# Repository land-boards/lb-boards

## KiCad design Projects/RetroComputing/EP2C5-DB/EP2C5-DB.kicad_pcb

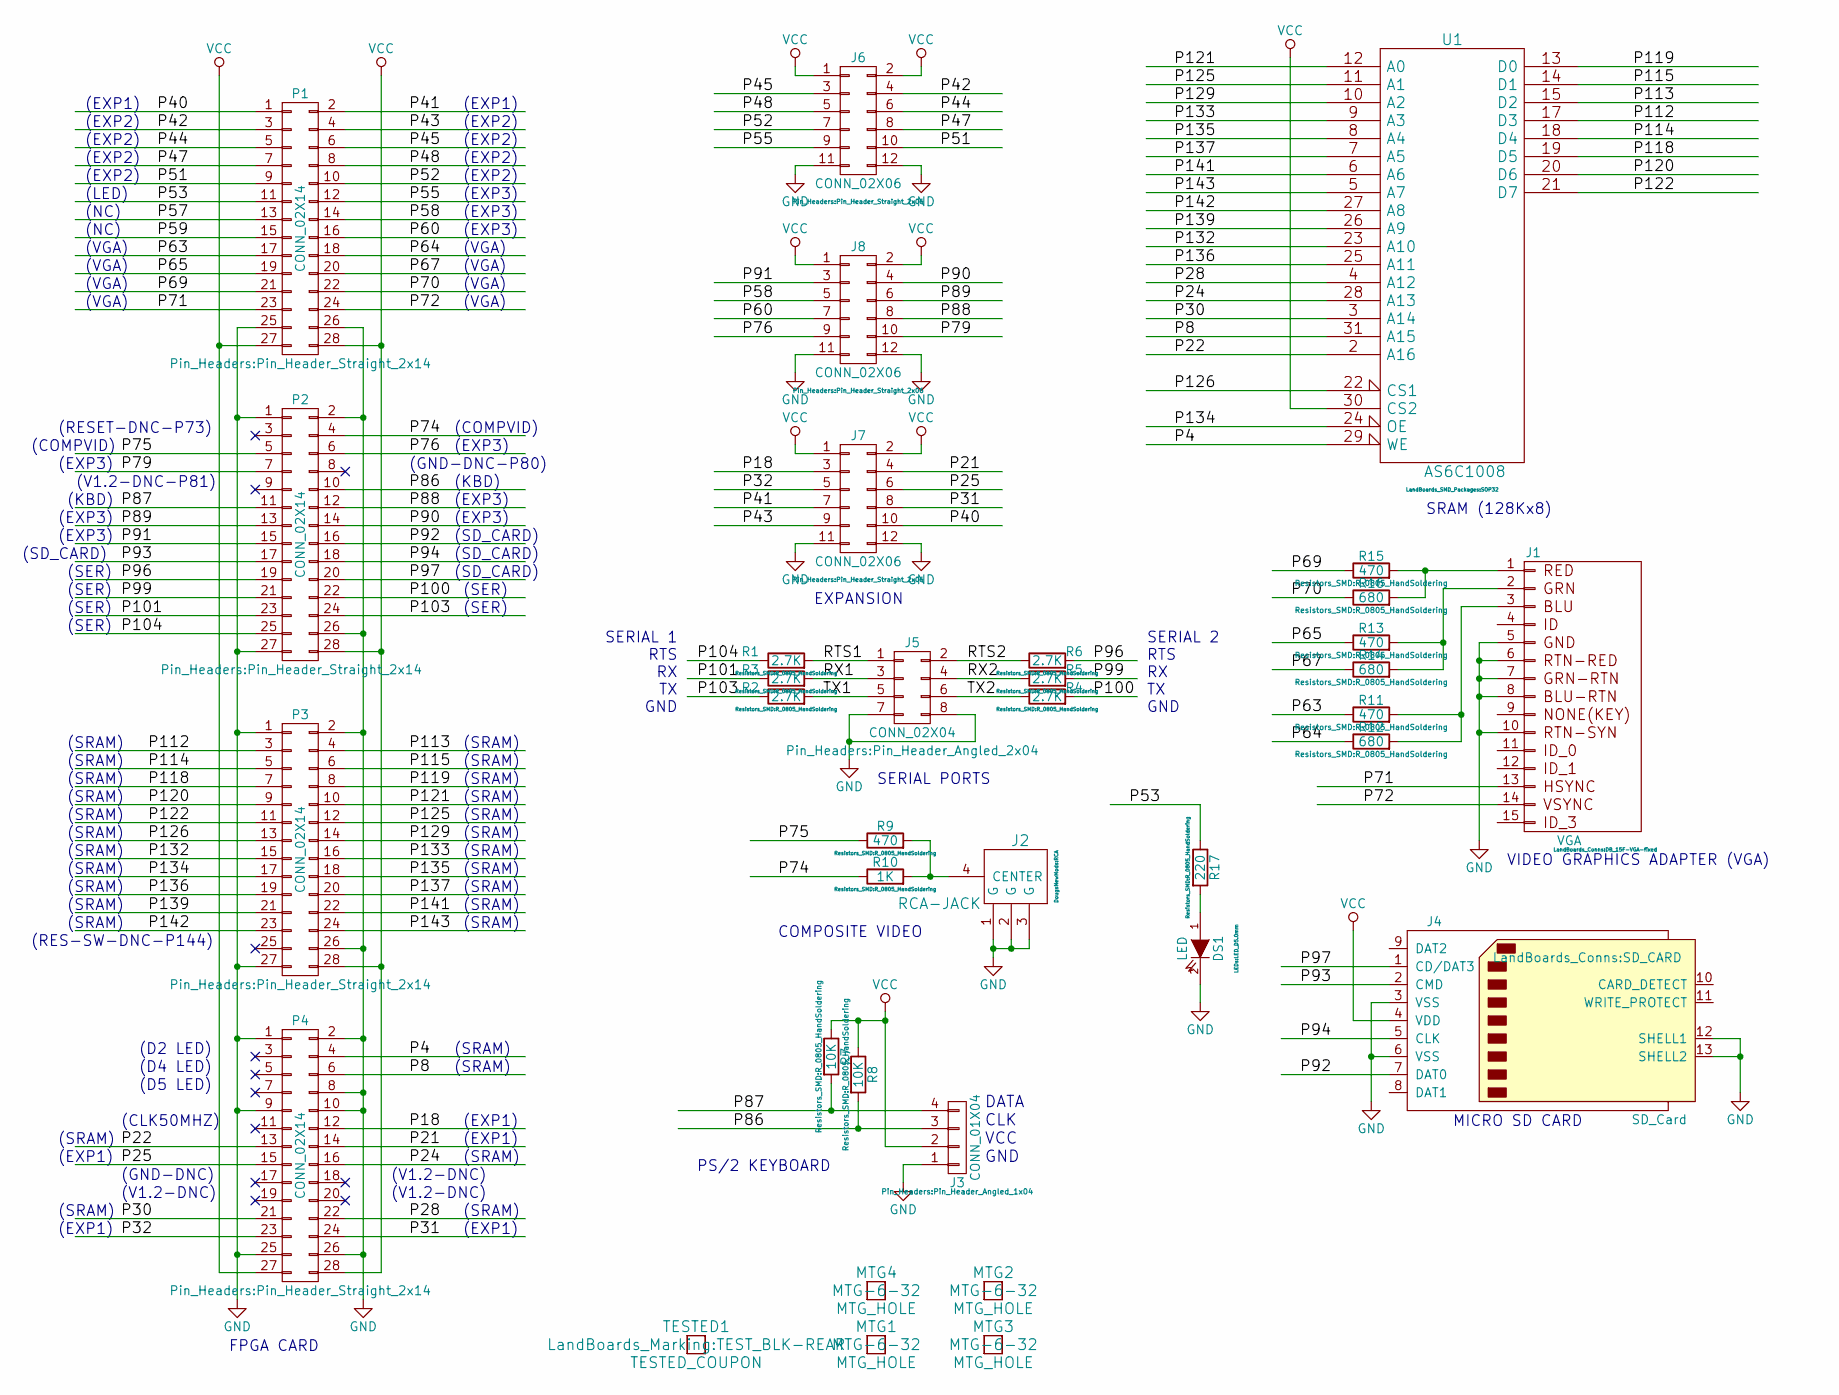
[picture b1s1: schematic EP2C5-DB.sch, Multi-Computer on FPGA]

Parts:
DS1: LED; LED_D5.0mm
J1: VGA; DB_15F-VGA-fixed
J2: RCA-JACK; RCA
J3: CONN_01X04; Pin_Header_Angled_1x04
J4: SD_Card; SD_CARD
J5: CONN_02X04; Pin_Header_Angled_2x04
J6, J7, J8: CONN_02X06; Pin_Header_Straight_2x06
MTG1, MTG2, MTG3, MTG4: MTG_HOLE; MTG-6-32
P1, P2, P3, P4: CONN_02X14; Pin_Header_Straight_2x14
R1, R2, R3, R4, R5, R6: 2.7K; R_0805_HandSoldering
R7, R8: 10K; R_0805_HandSoldering
R9, R11, R13, R15: 470; R_0805_HandSoldering
R10: 1K; R_0805_HandSoldering
R12, R14, R16: 680; R_0805_HandSoldering
R17: 220; R_0805_HandSoldering
TESTED1: TESTED_COUPON; TEST_BLK-REAR
U1: AS6C1008; SOP32

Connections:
/P4: P4.4, U1.29 (WE)
/P8: P4.6, U1.31 (A15)
/P18: J7.3, P4.12
/P21: J7.4, P4.14
/P22: P4.13, U1.2 (A16)
/P24: P4.16, U1.28 (A13)
/P25: J7.6, P4.15
/P28: P4.22, U1.4 (A12)
/P30: P4.21, U1.3 (A14)
/P31: J7.8, P4.24
/P32: J7.5, P4.23
/P40: J7.10, P1.1
/P41: J7.7, P1.2
/P42: J6.4, P1.3
/P43: J7.9, P1.4
/P44: J6.6, P1.5
/P45: J6.3, P1.6
/P47: J6.8, P1.7
/P48: J6.5, P1.8
/P51: J6.10, P1.9
/P52: J6.7, P1.10
/P53: P1.11, R17.1
/P55: J6.9, P1.12
/P58: J8.5, P1.14
/P60: J8.7, P1.16
/P63: P1.17, R11.1
/P64: P1.18, R12.1
/P65: P1.19, R13.1
/P67: P1.20, R14.1
/P69: P1.21, R15.1
/P70: P1.22, R16.1
/P71: J1.13, P1.23
/P72: J1.14, P1.24
/P74: P2.4, R10.1
/P75: P2.5, R9.1
/P76: J8.9, P2.6
/P79: J8.10, P2.7
/P86: J3.3, P2.10, R8.2
/P87: J3.4, P2.11, R7.2
/P88: J8.8, P2.12
/P89: J8.6, P2.13
/P90: J8.4, P2.14
/P91: J8.3, P2.15
/P92: J4.7 (DAT0), P2.16
/P93: J4.2 (CMD), P2.17
/P94: J4.5 (CLK), P2.18
/P96: P2.19, R6.2
/P97: J4.1 (CD/DAT3), P2.20
/P99: P2.21, R5.2
/P100: P2.22, R4.2
/P101: P2.23, R3.1
/P103: P2.24, R2.1
/P104: P2.25, R1.1
/P112: P3.3, U1.17 (D3)
/P113: P3.4, U1.15 (D2)
/P114: P3.5, U1.18 (D4)
/P115: P3.6, U1.14 (D1)
/P118: P3.7, U1.19 (D5)
/P119: P3.8, U1.13 (D0)
/P120: P3.9, U1.20 (D6)
/P121: P3.10, U1.12 (A0)
/P122: P3.11, U1.21 (D7)
/P125: P3.12, U1.11 (A1)
/P126: P3.13, U1.22 (CS1)
/P129: P3.14, U1.10 (A2)
/P132: P3.15, U1.23 (A10)
/P133: P3.16, U1.9 (A3)
/P134: P3.17, U1.24 (OE)
/P135: P3.18, U1.8 (A4)
/P136: P3.19, U1.25 (A11)
/P137: P3.20, U1.7 (A5)
/P139: P3.21, U1.26 (A9)
/P141: P3.22, U1.6 (A6)
/P142: P3.23, U1.27 (A8)
/P143: P3.24, U1.5 (A7)
/RTS1: J5.1, R1.2
/RTS2: J5.2, R6.1
/RX1: J5.3, R3.2
/RX2: J5.4, R5.1
/TX1: J5.5, R2.2
/TX2: J5.6, R4.1
GND: DS1.2 (K), J1.5, J1.6, J1.7, J1.8, J1.10, J2.1 (G), J2.2 (G), J2.3 (G), J3.1, J4.3 (VSS), J4.6 (VSS), J4.12 (SHELL1), J4.13 (SHELL2), J5.7, J5.8, J6.11, J6.12, J7.11, J7.12, J8.11, J8.12, P1.25, P1.26, P2.1, P2.2, P2.26, P2.27, P3.1, P3.2, P3.26, P3.27, P4.1, P4.2, P4.8, P4.9, P4.10, P4.25, P4.26, U1.16 (GND)
unnamed: DS1.1 (A), R17.2
unnamed: J1.1, R15.2, R16.2
unnamed: J1.2, R13.2, R14.2
unnamed: J1.3, R11.2, R12.2
unnamed: J2.4 (CENTER), R9.2, R10.2
VCC: J3.2, J4.4 (VDD), J6.1, J6.2, J7.1, J7.2, J8.1, J8.2, P1.27, P1.28, P2.28, P3.28, P4.27, P4.28, R7.1, R8.1, U1.30 (CS2), U1.32 (VCC)

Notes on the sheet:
SERIAL 1 RTS RX TX GND
SERIAL 2 RTS RX TX GND
DATA CLK VCC GND
PS/2 KEYBOARD
SRAM (128Kx8)
VIDEO GRAPHICS ADAPTER (VGA)
MICRO SD CARD
SERIAL PORTS
COMPOSITE VIDEO
FPGA CARD
EXPANSION
(CLK50MHZ)
(GND-DNC)
(GND-DNC-P80)
(V1.2-DNC-P81)
(D2 LED)
(D4 LED)
(D5 LED)
(RES-SW-DNC-P144)
(RESET-DNC-P73)
(V1.2-DNC)
(SRAM)
(EXP1)
(COMPVID)
(SD_CARD)
(KBD)
(SER)
(EXP2)
(EXP3)
(VGA)
(LED)
(NC)

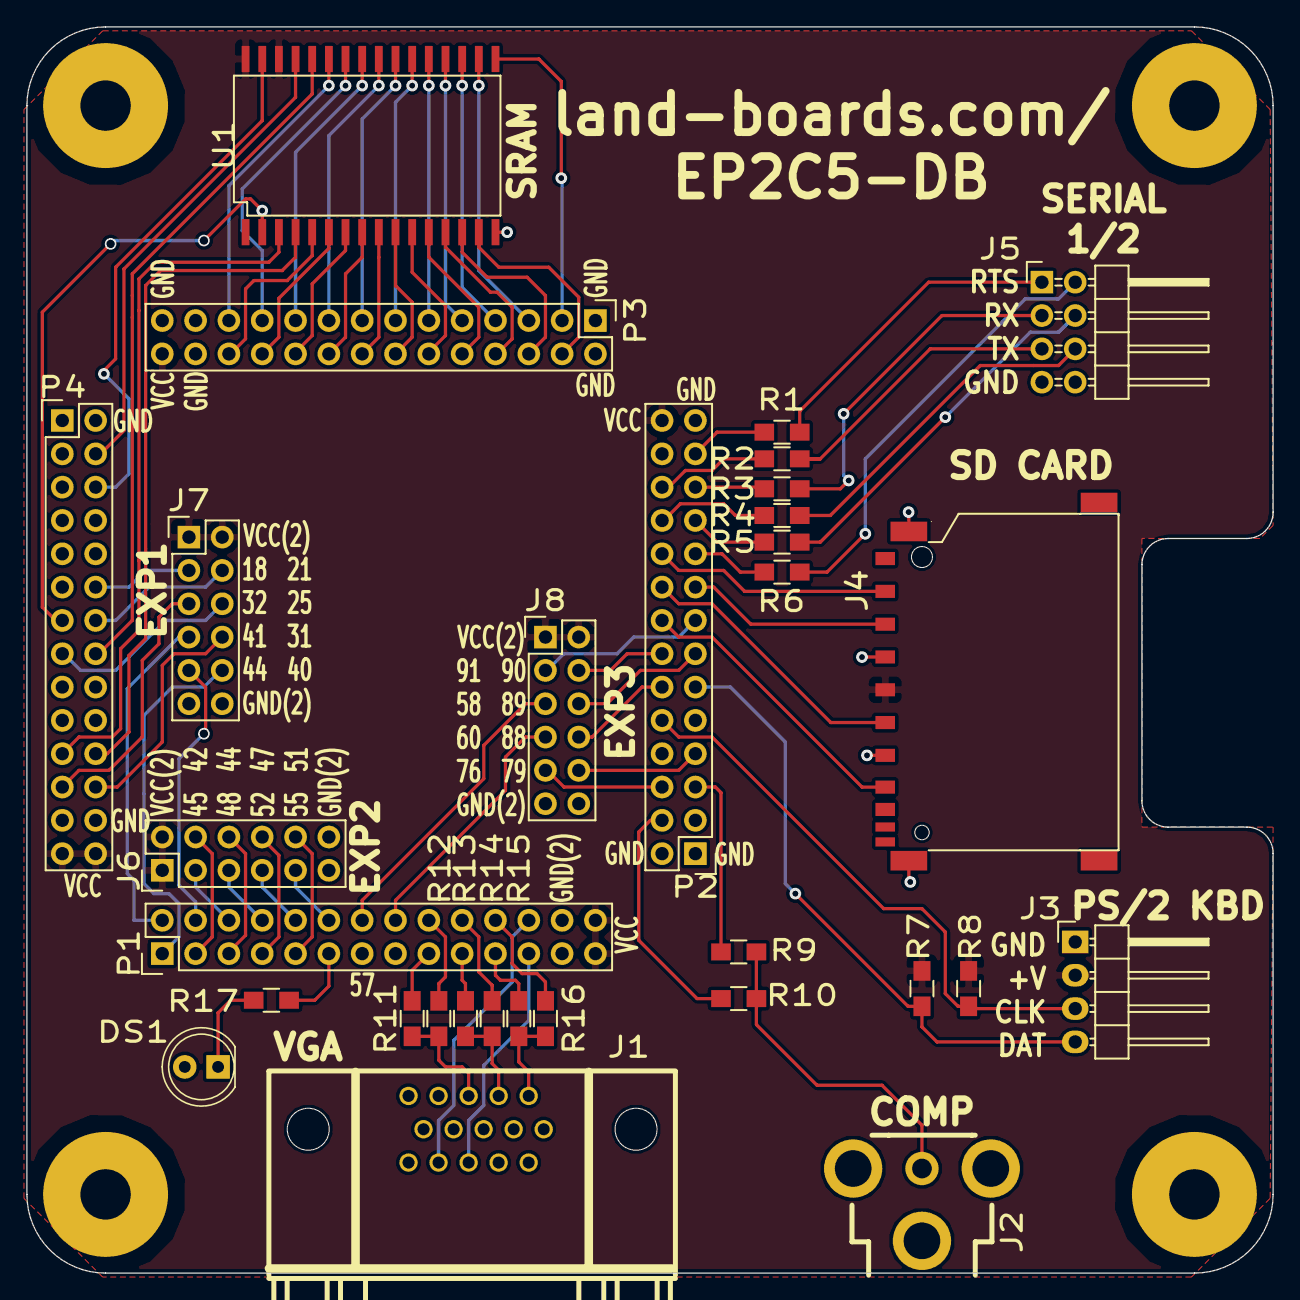
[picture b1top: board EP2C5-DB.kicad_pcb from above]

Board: 2 copper layers, 95.0 x 95.0 mm, 36 parts (0 on the bottom side), 88 nets.

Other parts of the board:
TESTED: TESTED_COUPON; TEST_BLK-REAR

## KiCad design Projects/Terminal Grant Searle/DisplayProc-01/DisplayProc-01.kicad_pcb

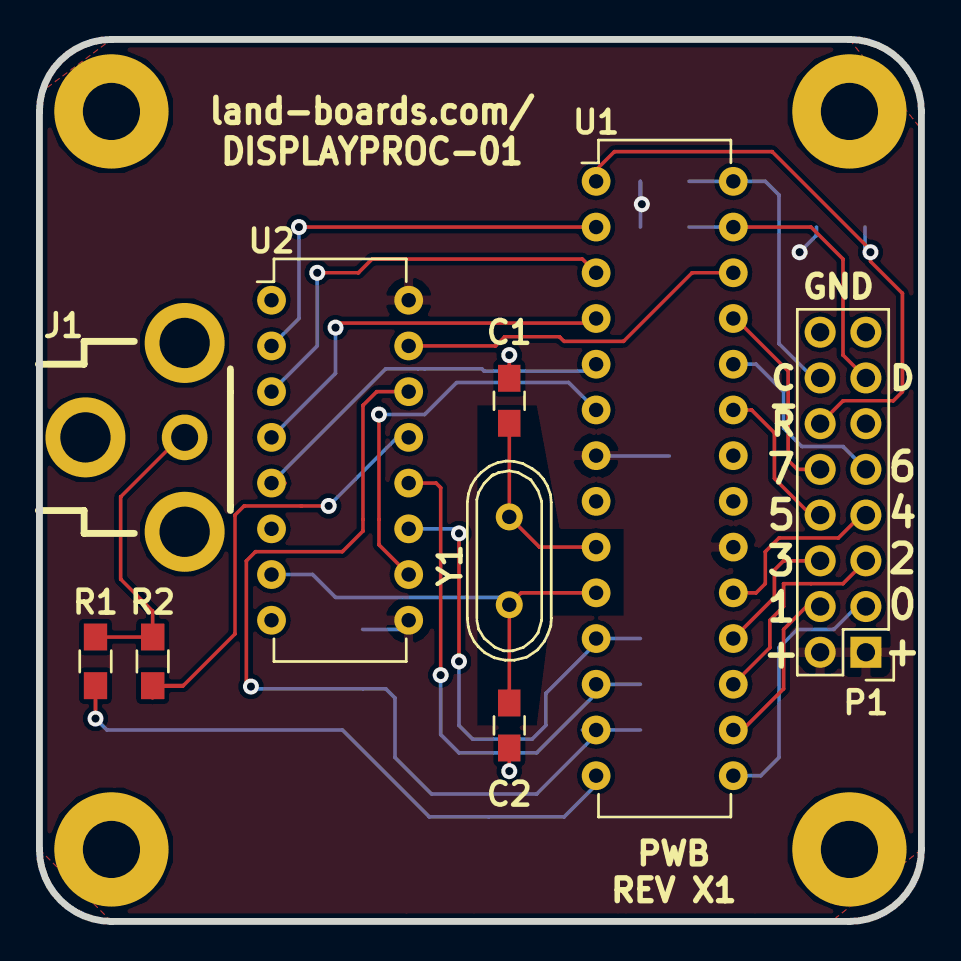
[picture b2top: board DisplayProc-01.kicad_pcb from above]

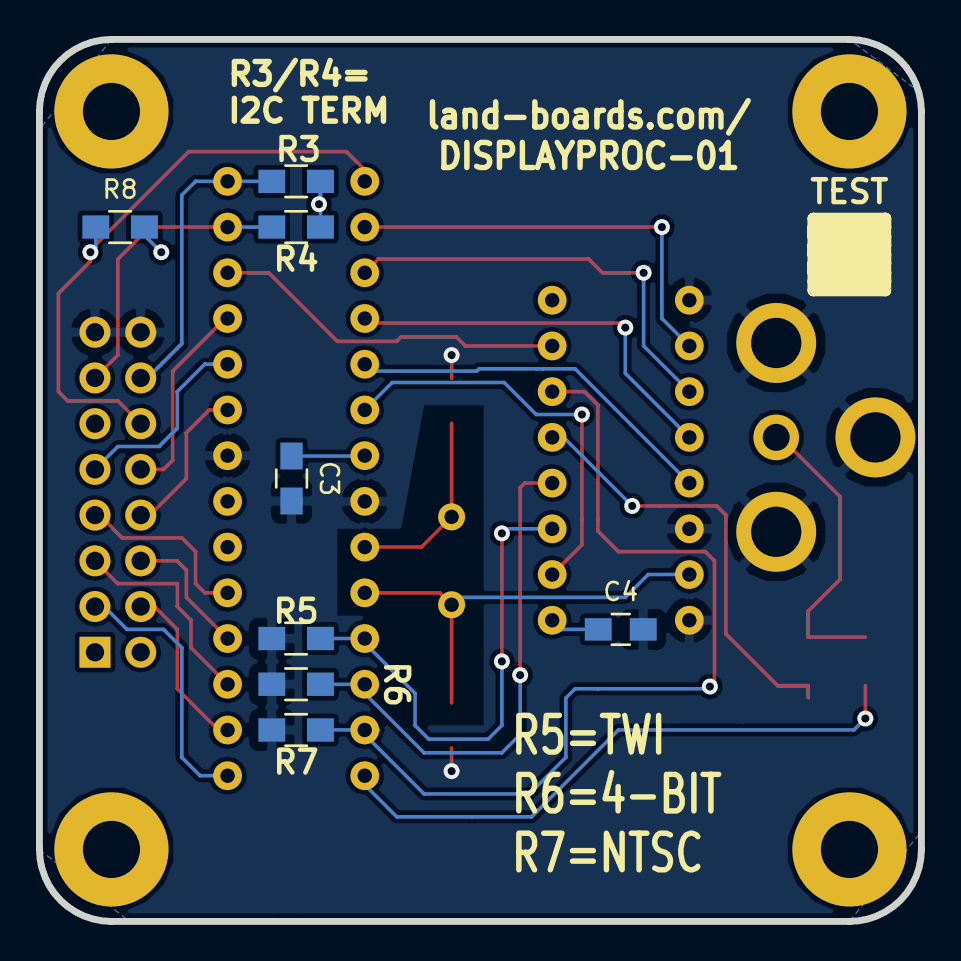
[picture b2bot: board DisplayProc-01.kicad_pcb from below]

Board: 2 copper layers, 49.0 x 49.0 mm, 22 parts (8 on the bottom side), 27 nets.

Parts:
C1, C2: 22pF; C_0805_HandSoldering
C3, C4: 0.1uF; C_0805_HandSoldering
J1: RCA-JACK; RCA
MTG1, MTG2, MTG3, MTG4: CONN_1; MTG-4-40
P1: CONN_02X08; Pin_Header_Straight_2x08
R1, R2: 470; R_0805_HandSoldering
R3, R4: OPEN; R_0805_HandSoldering
R5, R6, R7, R8: 10K; R_0805_HandSoldering
TEST: COUPON; TEST_BLK-REAR
U1: ATMEGA328-PU; DIP-28_W7.62mm
U2: 74HCT166; DIP-16_W7.62mm
Y1: 16MHz; Crystal_HC49-U_Vertical

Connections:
/ACKSDA: P1.13, R4.1, U1.27
/AVAILSCL: P1.14, R3.2, U1.28
/ID0: P1.3, U1.15
/ID1: P1.4, U1.16
/ID2: P1.5, U1.17
/ID3: P1.6, U1.18
/ID4: P1.7, U1.19
/ID5: P1.8, U1.23
/ID6: P1.9, U1.24
/ID7: P1.10, U1.25
/VD0: U1.2, U2.2
/VD1: U1.3, U2.3
/VD2: U1.4, U2.4
/VD3: U1.5, U2.5
/VD4: U1.6, U2.10
/VD5: R5.1, U1.11, U2.11
/VD6: R6.1, U1.12, U2.12
/VD7: R7.1, U1.13, U2.14
/~LD: U1.26, U2.15
/~RES: P1.12, R8.1, U1.1
GND: C1.2, C2.2, C3.2, C4.2, J1.1, J1.2, J1.3, P1.15, P1.16, R5.2, R6.2, R7.2, U1.8, U1.22, U2.1, U2.6, U2.8
unnamed: C1.1, U1.9, Y1.2
unnamed: C2.1, U1.10, U2.7, Y1.1
unnamed: J1.4, R1.1, R2.1
unnamed: R1.2, U1.14
unnamed: R2.2, U2.13
VCC: C3.1, C4.1, P1.1, P1.2, R3.1, R4.2, R8.2, U1.7, U1.20, U2.9, U2.16

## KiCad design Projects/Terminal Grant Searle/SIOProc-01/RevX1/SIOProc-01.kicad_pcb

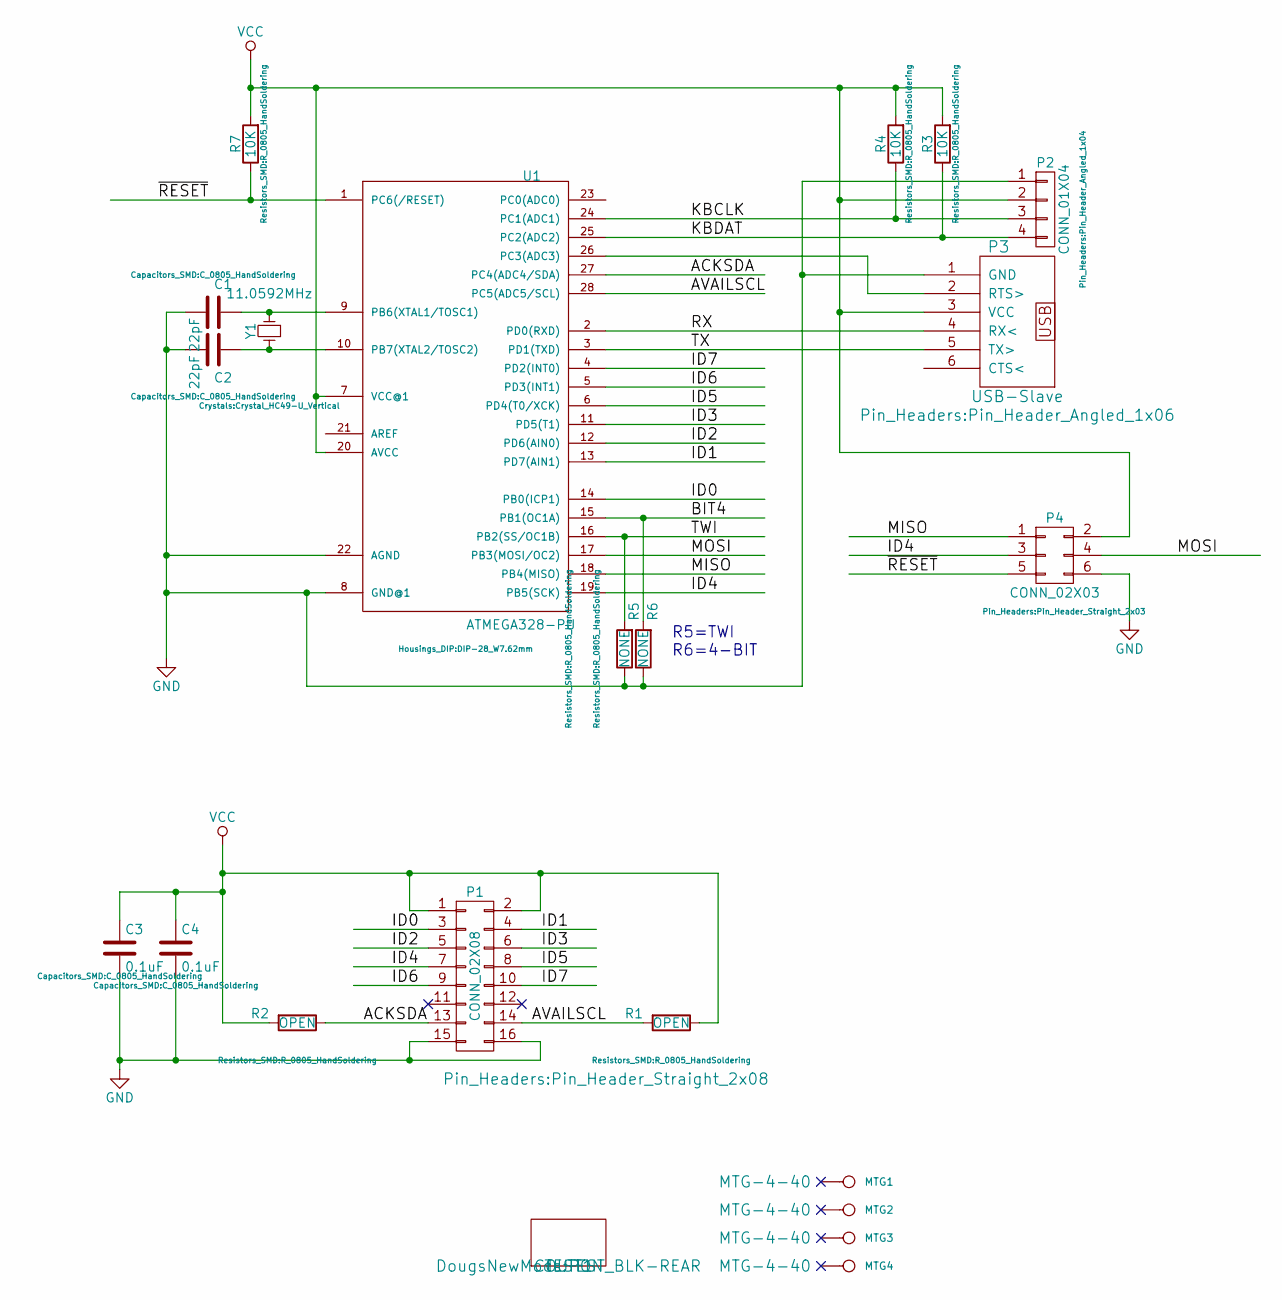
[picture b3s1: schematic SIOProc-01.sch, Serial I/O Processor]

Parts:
C1, C2: 22pF; C_0805_HandSoldering
C3, C4: 0.1uF; C_0805_HandSoldering
MTG1, MTG2, MTG3, MTG4: CONN_1; MTG-4-40
P1: CONN_02X08; Pin_Header_Straight_2x08
P2: CONN_01X04; Pin_Header_Angled_1x04
P3: USB-Slave; Pin_Header_Angled_1x06
P4: CONN_02X03; Pin_Header_Straight_2x03
R1, R2: OPEN; R_0805_HandSoldering
R3, R4, R7: 10K; R_0805_HandSoldering
R5, R6: NONE; R_0805_HandSoldering
TEST1: COUPON; TEST_BLK-REAR
U1: ATMEGA328-PU; DIP-28_W7.62mm
Y1: 11.0592MHz; Crystal_HC49-U_Vertical

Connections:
/ACKSDA: P1.13, R2.1, U1.27 (PC4(ADC4/SDA))
/AVAILSCL: P1.14, R1.2, U1.28 (PC5(ADC5/SCL))
/BIT4: R6.2, U1.15 (PB1(OC1A))
/ID0: P1.3, U1.14 (PB0(ICP1))
/ID1: P1.4, U1.13 (PD7(AIN1))
/ID2: P1.5, U1.12 (PD6(AIN0))
/ID3: P1.6, U1.11 (PD5(T1))
/ID4: P1.7, P4.3, U1.19 (PB5(SCK))
/ID5: P1.8, U1.6 (PD4(T0/XCK))
/ID6: P1.9, U1.5 (PD3(INT1))
/ID7: P1.10, U1.4 (PD2(INT0))
/KBCLK: P2.3, R4.1, U1.24 (PC1(ADC1))
/KBDAT: P2.4, R3.1, U1.25 (PC2(ADC2))
/MISO: P4.1, U1.18 (PB4(MISO))
/MOSI: P4.4, U1.17 (PB3(MOSI/OC2))
/RX: P3.4 (RX<), U1.2 (PD0(RXD))
/TWI: R5.2, U1.16 (PB2(SS/OC1B))
/TX: P3.5 (TX>), U1.3 (PD1(TXD))
/~RESET: P4.5, R7.1, U1.1 (PC6(/RESET))
GND: C1.2, C2.2, C3.2, C4.2, P1.15, P1.16, P2.1, P3.1 (GND), P4.6, R5.1, R6.1, U1.8 (GND@1), U1.22 (AGND)
unnamed: C1.1, U1.9 (PB6(XTAL1/TOSC1)), Y1.2
unnamed: C2.1, U1.10 (PB7(XTAL2/TOSC2)), Y1.1
VCC: C3.1, C4.1, P1.1, P1.2, P2.2, P3.3 (VCC), P4.2, R1.1, R2.2, R3.2, R4.2, R7.2, U1.7 (VCC@1), U1.20 (AVCC)

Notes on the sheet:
R5=TWI R6=4-BIT

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
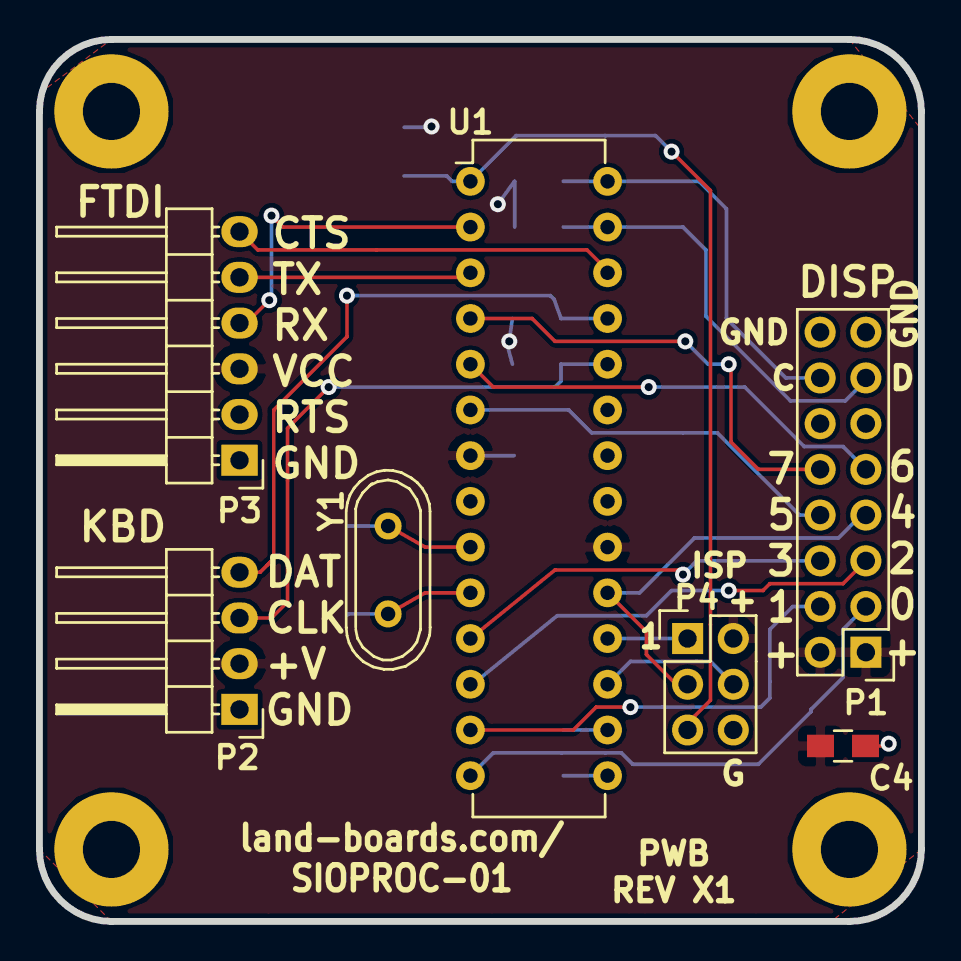
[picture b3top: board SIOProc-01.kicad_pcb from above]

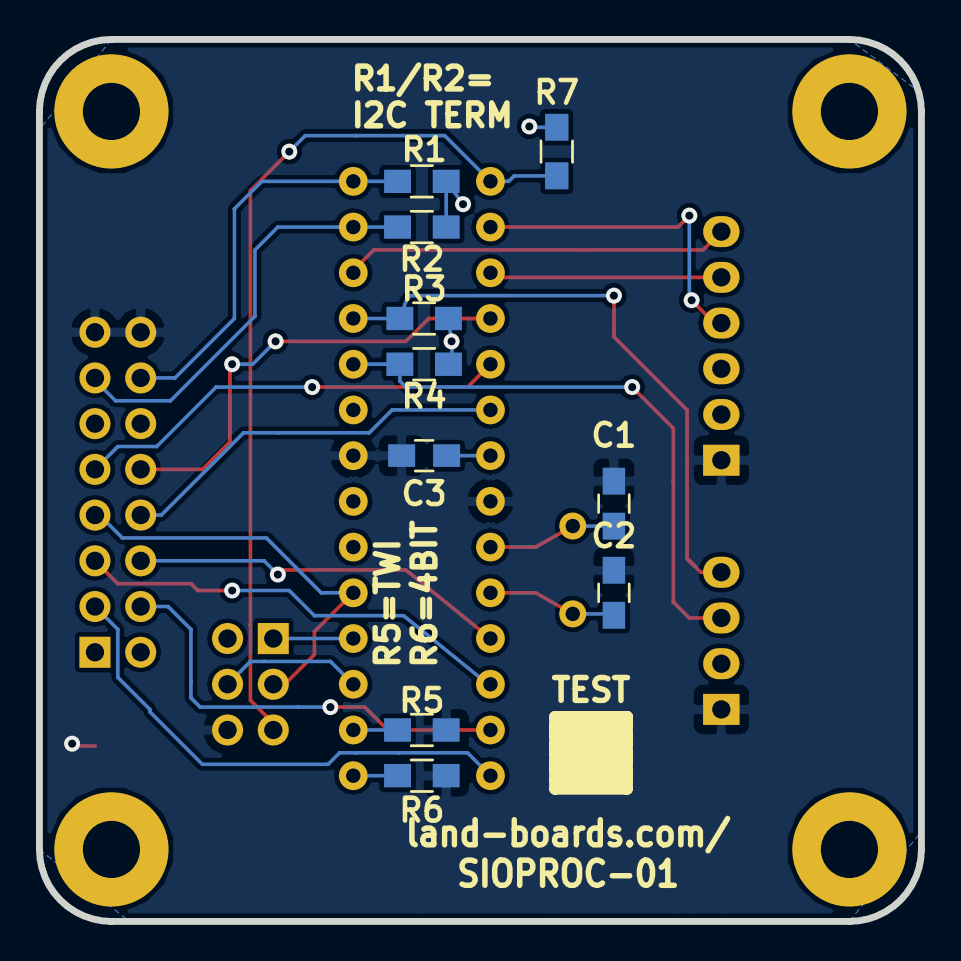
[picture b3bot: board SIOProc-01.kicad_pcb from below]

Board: 2 copper layers, 49.0 x 49.0 mm, 22 parts (10 on the bottom side), 24 nets.

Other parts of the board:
TEST: COUPON; TEST_BLK-REAR

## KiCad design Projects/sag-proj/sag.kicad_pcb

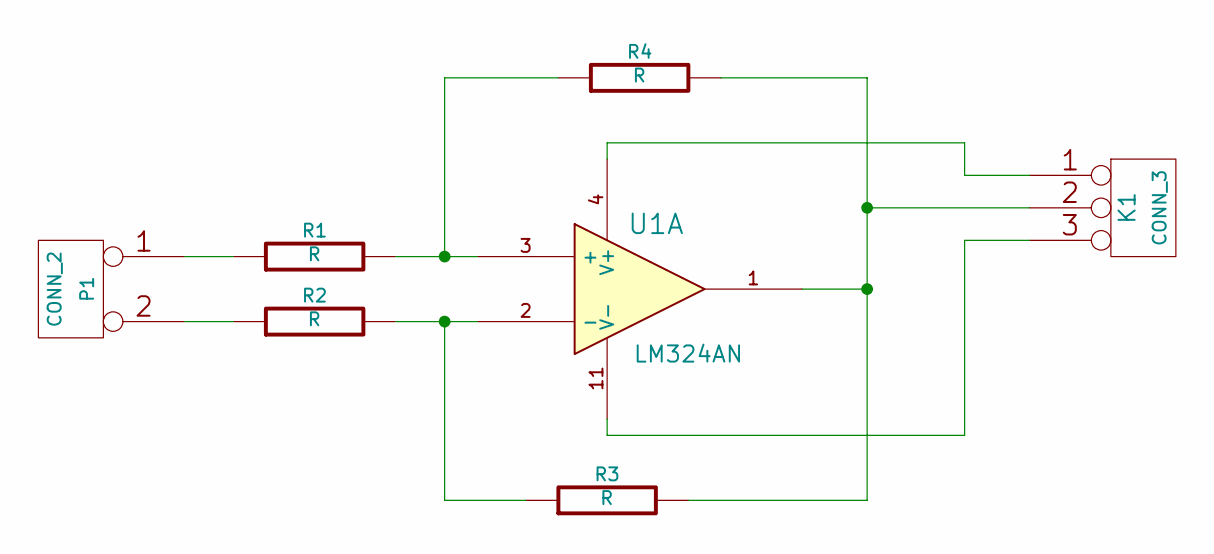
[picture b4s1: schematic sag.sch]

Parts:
K1: CONN_3
P1: CONN_2
R1, R2, R3, R4: R
U1: LM324AN

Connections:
unnamed: K1.2 (PM), R3.2, R4.2, U1.1
unnamed: P1.1, R1.1
unnamed: P1.2 (PM), R2.1
unnamed: K1.1, U1.4 (V+)
unnamed: K1.3, U1.11 (V-)
unnamed: R1.2, R4.1, U1.3 (+)
unnamed: R2.2, R3.1, U1.2 (-)

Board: 2 copper layers, 7 parts (0 on the bottom side), 7 nets, no tracks yet.

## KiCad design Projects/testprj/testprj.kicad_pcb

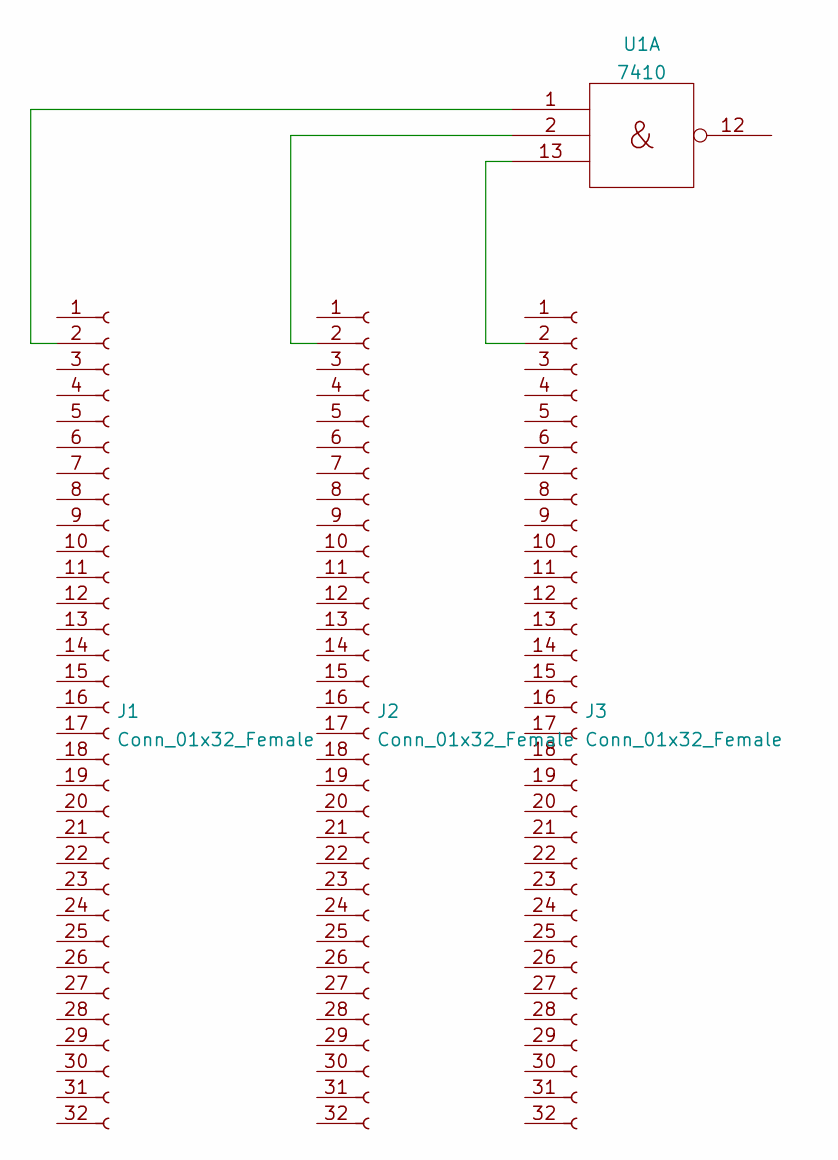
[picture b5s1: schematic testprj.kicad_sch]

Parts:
J1, J2, J3: Conn_01x32_Female; PinHeader_1x32_P2.54mm_Vertical
U1: 7410; DIP-14_W7.62mm

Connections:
Gnd: U1.7 (Gnd)
unnamed: J1.2, U1.1
unnamed: J2.2, U1.2
unnamed: J3.2, U1.13
Vcc: U1.14 (Vcc)

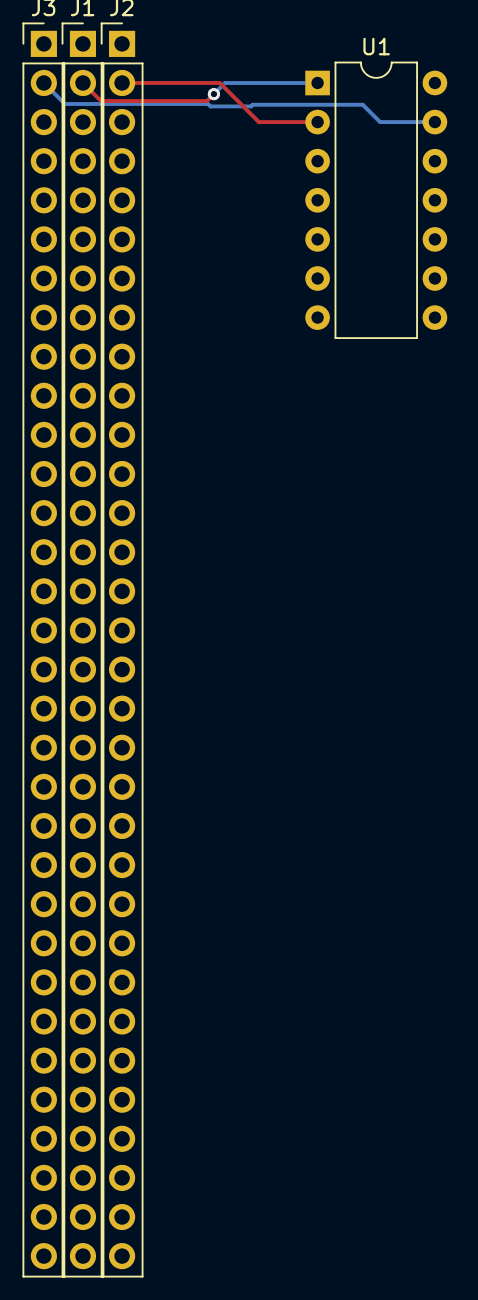
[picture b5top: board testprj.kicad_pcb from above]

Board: 2 copper layers, 4 parts (0 on the bottom side), 3 nets.

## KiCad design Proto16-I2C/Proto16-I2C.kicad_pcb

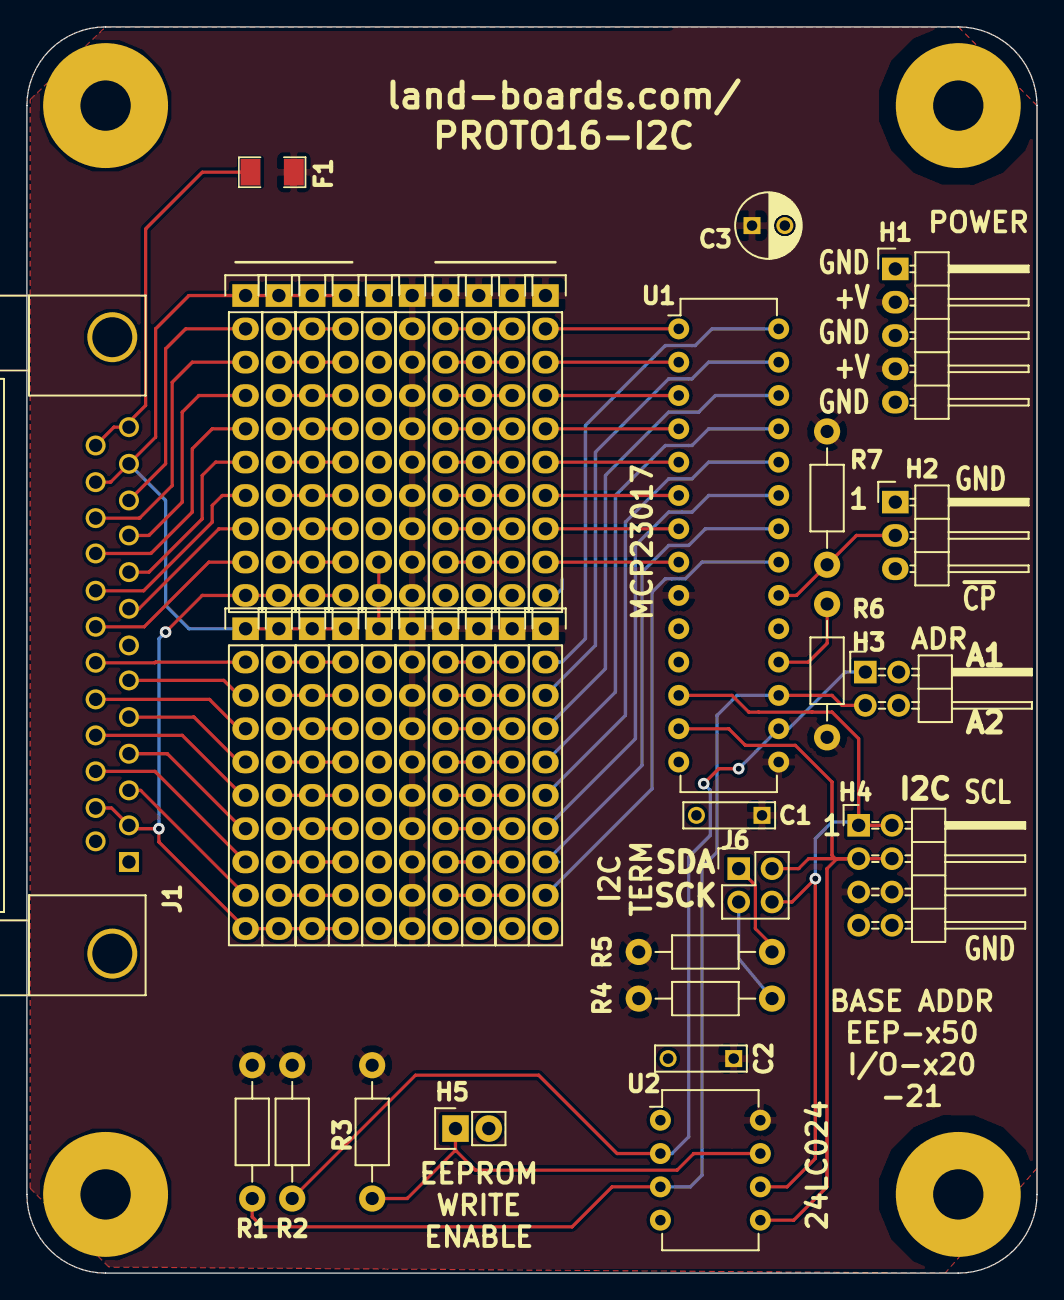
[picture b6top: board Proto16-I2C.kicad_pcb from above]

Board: 2 copper layers, 77.0 x 95.0 mm, 45 parts (0 on the bottom side), 78 nets.

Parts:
C1, C2: 0.1uF; C_Rect_L7_W2_P5
C3: 47uF; C_Radial_D5_L11_P2.5
F1: FUSE; SM1206
H1: CONN_01X05; Pin_Header_Angled_1x05
H2: CONN_01X03; Pin_Header_Angled_1x03
H3: CONN_02X02; Pin_Header_Angled_2x02
H4: CONN_02X04; Pin_Header_Angled_2x04
H5: CONN_01X02; Pin_Header_Straight_1x02
J1: DB25; DB25FC
J6: CONN_02X02; Pin_Header_Straight_2x02
MTG1, MTG2, MTG3, MTG4: MTG_HOLE; MTG-6-32
P1, P3, P4, P5, P6, P7, P8, P9, P10, P11, P12, P13, P14, P15, P16, P17, P18, P19, P20, P99: CONN_01X10; Pin_Header_Straight_1x10
R1, R2, R6, R7: 10K; Resistor_Horizontal_RM10mm
R3: 1K; Resistor_Horizontal_RM10mm
R4, R5: 2.2K; Resistor_Horizontal_RM10mm
TESTED: TESTED_COUPON; TEST_BLK-REAR
U1: MCP23017P; DIP-28_W7.62mm
U2: 24C01; DIP-8_W7.62mm

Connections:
+5V: C1.1, C2.1, C3.1, F1.1, H1.2, H1.4, H4.5, H4.6, P1.1, P3.1, P4.1, P5.1, P5.2, P5.3, P5.4, P5.5, P5.6, P5.7, P5.8, P5.9, P5.10, P6.1, P6.2, P6.3, P6.4, P6.5, P6.6, P6.7, P6.8, P6.9, P6.10, P7.1, P10.1, P19.1, P20.1, P99.1, R1.2, R2.2, R3.2, R4.2, R5.2, R6.2, R7.2, U1.9, U1.15, U2.8
/A1: H3.1, R2.1, U1.16, U2.2
/A2: H3.3, R1.1, U1.17, U2.3
/INT1: H2.2, R7.1, U1.20
/RST: R6.1, U1.18
/SCL: H4.1, H4.2, J6.4, U1.12, U2.6
/SDA: H4.3, H4.4, J6.2, U1.13, U2.5
GND: C1.2, C2.2, C3.2, H1.1, H1.3, H1.5, H2.1, H2.3, H3.2, H3.4, H4.7, H4.8, H5.2, J1.1, J1.14, P1.10, P3.10, P4.10, P7.10, P8.1, P8.2, P8.3, P8.4, P8.5, P8.6, P8.7, P8.8, P8.9, P8.10, P9.1, P9.2, P9.3, P9.4, P9.5, P9.6, P9.7, P9.8, P9.9, P9.10, P10.10, P19.10, P20.10, P99.10, U1.10, U2.1, U2.4
unnamed: F1.2, J1.13, J1.25
unnamed: H5.1, R3.1, U2.7
unnamed: J6.1, R5.1
unnamed: J6.3, R4.1
unnamed: J1.3, P18.9
unnamed: J1.4, P18.7
unnamed: J1.5, P18.5
unnamed: J1.6, P18.3
unnamed: J1.8, P17.8
unnamed: J1.9, P17.6
unnamed: J1.10, P17.4
unnamed: J1.11, P17.2
unnamed: J1.12, J1.24, P11.1, P12.1, P13.1, P14.1, P15.1, P16.1, P17.1, P18.1
unnamed: J1.2, J1.15, P11.10, P12.10, P13.10, P14.10, P15.10, P16.10, P17.10, P18.10
unnamed: J1.16, P18.8
unnamed: J1.17, P18.6
unnamed: J1.18, P18.4
unnamed: J1.19, P18.2
unnamed: J1.20, P17.9
unnamed: J1.21, P17.7
unnamed: J1.22, P17.5
unnamed: J1.23, P17.3
unnamed: P1.2, P3.2, P7.2
unnamed: P1.3, P3.3, P7.3
unnamed: P1.4, P3.4, P7.4
unnamed: P1.5, P3.5, P7.5
unnamed: P1.6, P3.6, P7.6
unnamed: P1.7, P3.7, P7.7
unnamed: P1.8, P3.8, P7.8
unnamed: P1.9, P3.9, P7.9
unnamed: P4.2, P10.2, P99.2
unnamed: P4.3, P10.3, P99.3
unnamed: P4.4, P10.4, P99.4
unnamed: P4.5, P10.5, P99.5
unnamed: P4.6, P10.6, P99.6
unnamed: P4.7, P10.7, P99.7
unnamed: P4.8, P10.8, P99.8
unnamed: P4.9, P10.9, P99.9
unnamed: P11.2, P13.2, P16.2
unnamed: P11.3, P13.3, P16.3
unnamed: P11.4, P13.4, P16.4
unnamed: P11.5, P13.5, P16.5
unnamed: P11.6, P13.6, P16.6
unnamed: P11.7, P13.7, P16.7
unnamed: P11.8, P13.8, P16.8
unnamed: P11.9, P13.9, P16.9
unnamed: P12.2, P14.2, P15.2
unnamed: P12.3, P14.3, P15.3
unnamed: P12.4, P14.4, P15.4
unnamed: P12.5, P14.5, P15.5
unnamed: P12.6, P14.6, P15.6
unnamed: P12.7, P14.7, P15.7
unnamed: P12.8, P14.8, P15.8
unnamed: P12.9, P14.9, P15.9
unnamed: P19.2, U1.28
unnamed: P19.3, U1.27
unnamed: P19.4, U1.26
unnamed: P19.5, U1.25
unnamed: P19.6, U1.24
unnamed: P19.7, U1.23
unnamed: P19.8, U1.22
unnamed: P19.9, U1.21
unnamed: P20.2, U1.1
unnamed: P20.3, U1.2
unnamed: P20.4, U1.3
unnamed: P20.5, U1.4
unnamed: P20.6, U1.5
unnamed: P20.7, U1.6
unnamed: P20.8, U1.7
unnamed: P20.9, U1.8
